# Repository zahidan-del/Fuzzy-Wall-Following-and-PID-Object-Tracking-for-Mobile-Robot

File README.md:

# Fuzzy Wall-Following and PID Object Tracking on Mobile Robot

This repository contains a **mobile robot** project with a hybrid control system combining a **Fuzzy Logic Controller** for wall-following navigation and a **PID Controller** for camera-based object tracking. The system uses a distributed architecture where the **Raspberry Pi 4 Model B** handles image processing and PID computation, while the **ESP32 Devkit V1** controls the actuators in real-time based on fuzzy logic and commands from the Raspberry Pi.  

---

## Key Features
- Wall-following navigation using **Fuzzy Logic Controller** based on VL53L0X distance sensor.  
- Camera-based object tracking using **PID Controller**.  
- **Raspberry Pi** integration for computer vision and **ESP32** for motor control.  
- Multi-tasking system capable of performing navigation and object tracking simultaneously.  
- Object detection based on HSV (*Hue, Saturation, Value*) for high accuracy under various lighting conditions.  

---

## Technologies Used
- **Raspberry Pi 4 Model B** – Computer vision processing and PID computation.  
- **ESP32 Devkit V1** – Real-time actuator control and fuzzy logic execution.  
- **Fuzzy Logic Controller (FLC)** – Handles uncertainty and non-linearity in robot navigation.  
- **PID Controller** – Adjusts robot’s speed and direction during object tracking.  
- **OpenCV (Python)** – HSV-based object detection from Raspberry Pi camera.  
- **Serial Communication (UART)** – Connects Raspberry Pi with ESP32.  

---

## Main Components Used
- **Raspberry Pi 4 Model B**  
- **ESP32 Devkit V1**  
- **SG90 Servo Motor** (for gripper control)  
- **Pi Camera** (Raspberry Pi camera for computer vision)  
- **N30 Micro Gear DC Motor** (wheel drive)  
- **L298N Motor Driver**  
- **XL4016 Step Down Converter** (voltage regulation)  
- **18650 Battery (x3)**  
- **3S 18650 Battery Holder**  

---

## Contact
📧 Email: [zahidan54@gmail.com](mailto:zhdn54@gmail.com)  
📷 Instagram: [@zhdnakhmad](https://instagram.com/zhdnakhmad)

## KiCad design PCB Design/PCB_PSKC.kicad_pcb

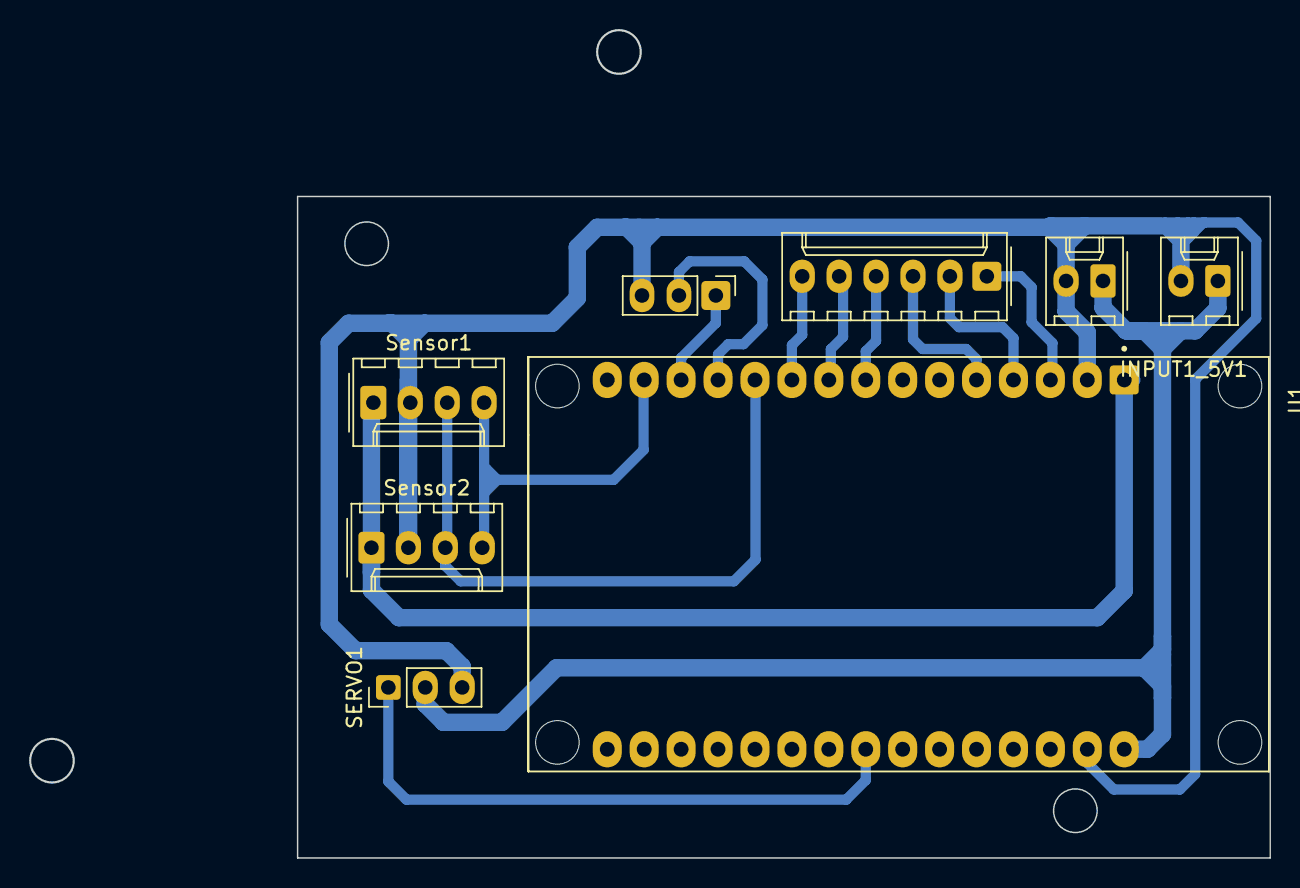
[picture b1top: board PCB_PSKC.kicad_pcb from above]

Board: 2 copper layers, 85.3 x 56.9 mm, 8 parts (0 on the bottom side), 14 nets.

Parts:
COMMUNICATION1: Conn_01x03_Male; PinHeader_1x03_P2.54mm_Vertical
INPUT1_5V1: Conn_01x02_Male; Molex_KK-254_AE-6410-02A_1x02_P2.54mm_Vertical
INPUT_RASP1_5V1: Conn_01x02_Male; Molex_KK-254_AE-6410-02A_1x02_P2.54mm_Vertical
L298N1: Conn_01x06_Male; Molex_KK-254_AE-6410-06A_1x06_P2.54mm_Vertical
SERVO1: Conn_01x03_Male; PinHeader_1x03_P2.54mm_Vertical
Sensor1, Sensor2: Conn_01x04_Pin; Molex_KK-254_AE-6410-04A_1x04_P2.54mm_Vertical
U1: ESP32-DEVKIT-V1; MODULE_ESP32_DEVKIT_V1

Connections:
EN1: L298N1.1, U1.3 (D15)
EN2: L298N1.6, U1.10 (D19)
IN1: L298N1.2, U1.4 (D2)
IN2: L298N1.3, U1.5 (D4)
IN3: L298N1.4, U1.8 (D5)
IN4: L298N1.5, U1.9 (D18)
unnamed: COMMUNICATION1.3, INPUT1_5V1.2, INPUT_RASP1_5V1.2, SERVO1.3, Sensor1.2, Sensor2.2, U1.2 (GND), U1.29 (GND)
unnamed: INPUT1_5V1.1, INPUT_RASP1_5V1.1, SERVO1.2, U1.30 (VIN)
unnamed: Sensor1.1, Sensor2.1, U1.1 (3V3)
RX0: COMMUNICATION1.2, U1.12 (RX0)
SCL: Sensor1.3, Sensor2.3, U1.11 (D21)
SDA: Sensor1.4, Sensor2.4, U1.14 (D22)
Servo1: SERVO1.1, U1.23 (D25)
TX0: COMMUNICATION1.1, U1.13 (TX0)
